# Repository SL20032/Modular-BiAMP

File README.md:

# Modular-BiAMP
Sample Modular Bi-AMP designed to work with Technics HD501 speakers (bc ampilifre in mine died). Project in active development.

## Modules
- Crosover PCB - Simple Active opamp based crosover providing 80db/dec attenuation. Components selected for 20 Hz to 3kHz passband for low freq part and 3kHz to 20kHz passband for high freq part.
- Power Amp PCB - Amplifire (AB-class) board using LM3886 for low frequence part (woofers) and LM4766 for high Frequency parts (tweeters)

## Fotos

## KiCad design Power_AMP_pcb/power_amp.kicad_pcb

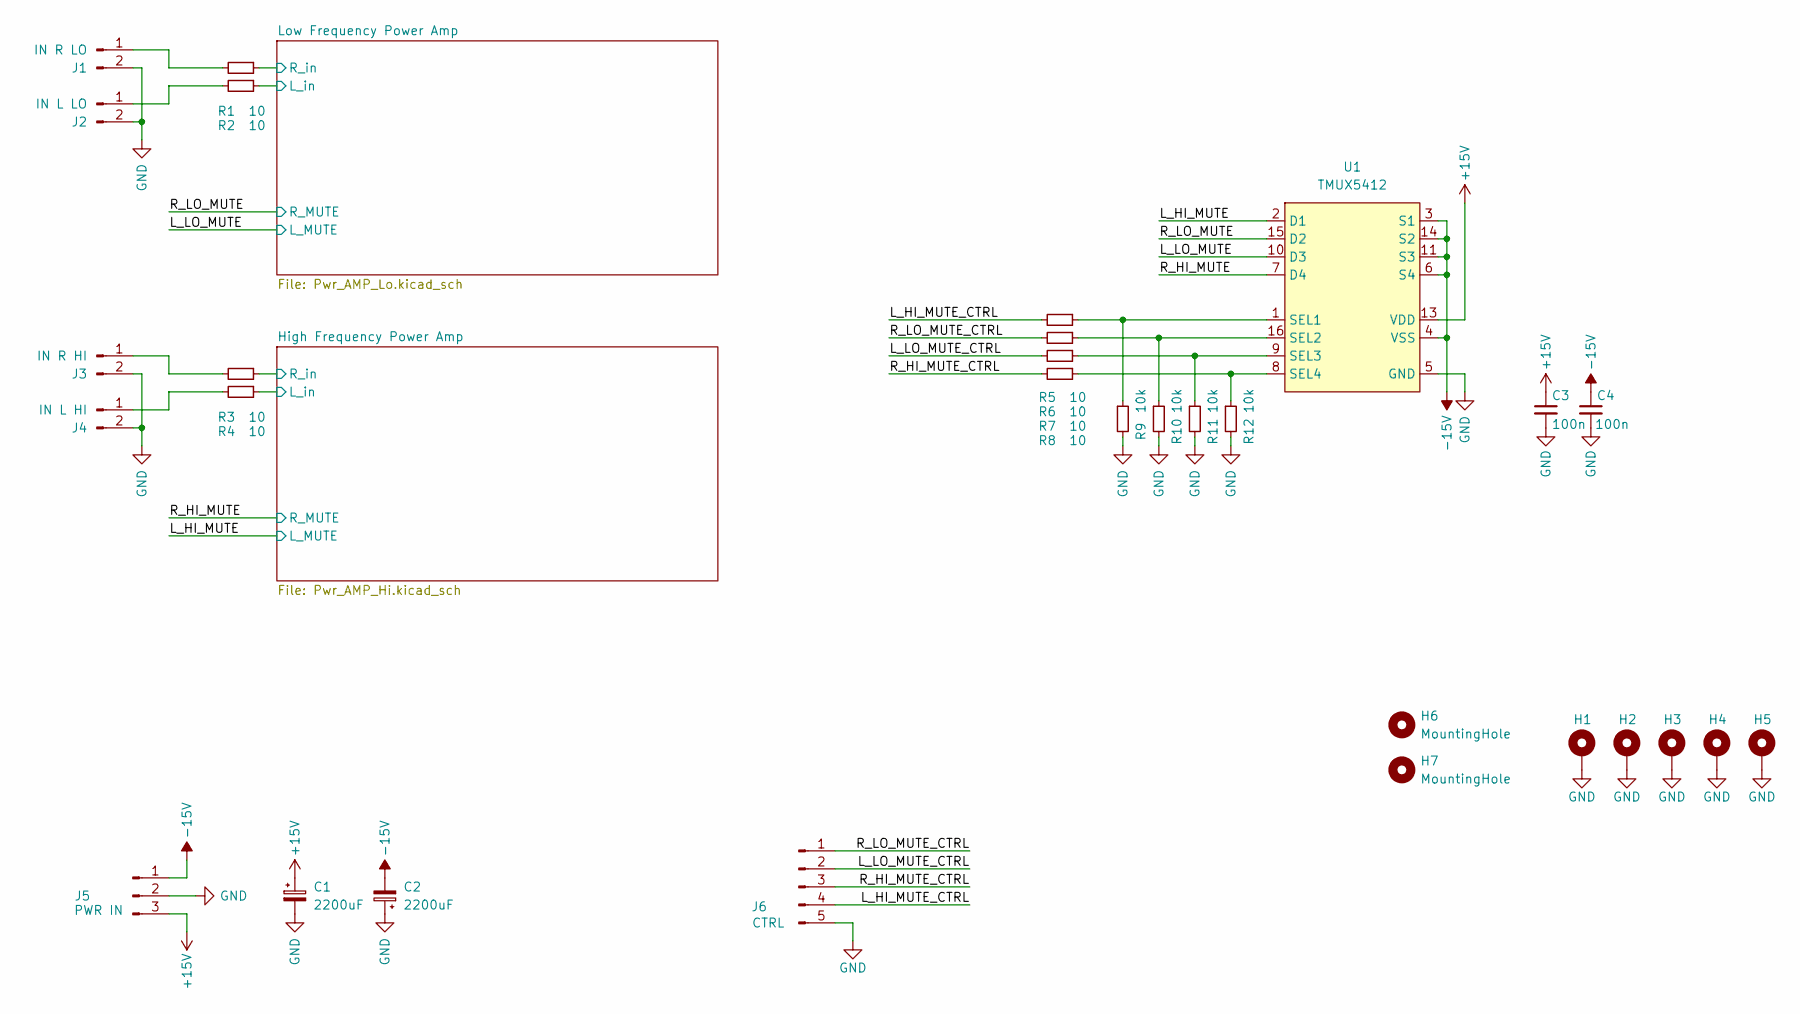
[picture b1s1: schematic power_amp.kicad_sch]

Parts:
C1, C2: 2200uF; CP_Radial_D12.5mm_P5.00mm
C3, C4: 100n; C_0805_2012Metric_Pad1.18x1.45mm_HandSolder
H1, H2, H3, H4, H5: MountingHole_Pad; MountingHole_3.2mm_M3_DIN965_Pad
H6, H7: MountingHole; Mounting_slots
J1: IN R LO; JST_NV_B02P-NV_1x02_P5.00mm_Vertical
J2: IN L LO; JST_NV_B02P-NV_1x02_P5.00mm_Vertical
J3: IN R HI; JST_NV_B02P-NV_1x02_P5.00mm_Vertical
J4: IN L HI; JST_NV_B02P-NV_1x02_P5.00mm_Vertical
J5: PWR IN; JST_NV_B03P-NV_1x03_P5.00mm_Vertical
J6: CTRL; PinHeader_1x05_P2.54mm_Vertical
R1, R2, R3, R4, R5, R6, R7, R8: 10; R_0805_2012Metric_Pad1.20x1.40mm_HandSolder
R9, R10, R11, R12: 10k; R_0805_2012Metric_Pad1.20x1.40mm_HandSolder
U1: TMUX5412; TSSOP-16_4.4x5mm_P0.65mm

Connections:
+15V: C1.1, C3.1, J5.3, U1.13 (VDD); also elsewhere on the board
-15V: C2.2, C4.1, J5.1, U1.3 (S1), U1.4 (VSS), U1.6 (S4), U1.11 (S3), U1.14 (S2); also elsewhere on the board
/High Frequency Power Amp/L_in: R4.1; also elsewhere on the board
/High Frequency Power Amp/R_in: R3.1; also elsewhere on the board
/L_HI_MUTE: U1.2 (D1); also elsewhere on the board
/L_HI_MUTE_CTRL: J6.4, R5.2
/L_LO_MUTE: U1.10 (D3); also elsewhere on the board
/L_LO_MUTE_CTRL: J6.2, R7.2
/Low Frequency Power Amp/L_in: R2.1; also elsewhere on the board
/Low Frequency Power Amp/R_in: R1.1; also elsewhere on the board
/R_HI_MUTE: U1.7 (D4); also elsewhere on the board
/R_HI_MUTE_CTRL: J6.3, R8.2
/R_LO_MUTE: U1.15 (D2); also elsewhere on the board
/R_LO_MUTE_CTRL: J6.1, R6.2
GND: C1.2, C2.1, C3.2, C4.2, H1.1, H2.1, H3.1, H4.1, H5.1, J1.2, J2.2, J3.2, J4.2, J5.2, J6.5, R9.2, R10.2, R11.2, R12.2, U1.5 (GND); also elsewhere on the board
unnamed: J1.1, R1.2
unnamed: J2.1, R2.2
unnamed: J3.1, R3.2
unnamed: J4.1, R4.2
unnamed: R5.1, R9.1, U1.1 (SEL1)
unnamed: R6.1, R10.1, U1.16 (SEL2)
unnamed: R7.1, R11.1, U1.9 (SEL3)
unnamed: R8.1, R12.1, U1.8 (SEL4)

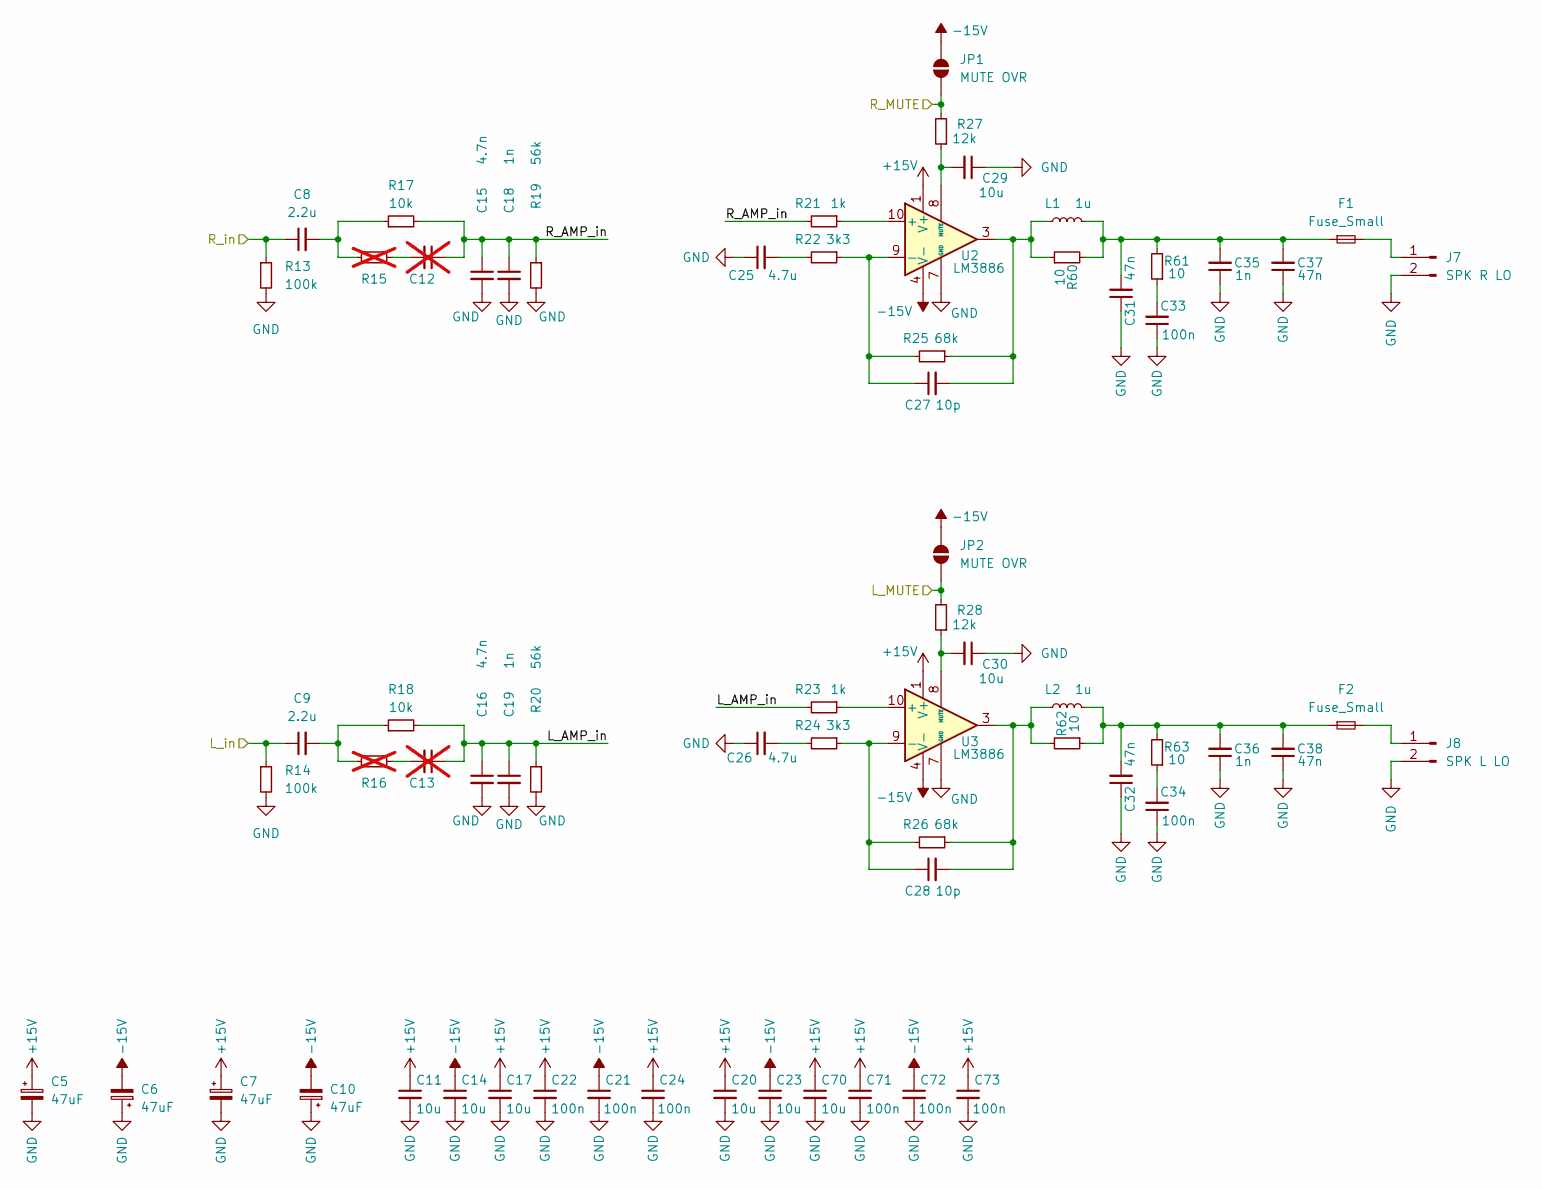
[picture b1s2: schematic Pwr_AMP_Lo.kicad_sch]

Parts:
C5, C6, C7, C10: 47uF; CP_Radial_D8.0mm_P3.50mm
C8, C9: 2.2u; C_Rect_L11.0mm_W5.1mm_P10.00mm_MKT
C11, C14, C17, C20, C23, C70: 10u; C_0805_2012Metric_Pad1.18x1.45mm_HandSolder
C12, C13: C_0805_2012Metric_Pad1.18x1.45mm_HandSolder; not fitted
C15, C16: 4.7n; C_Rect_L7.2mm_W2.5mm_P5.00mm_FKS2_FKP2_MKS2_MKP2
C18, C19, C35, C36: 1n; C_Rect_L7.2mm_W2.5mm_P5.00mm_FKS2_FKP2_MKS2_MKP2
C21, C22, C24, C71, C72, C73: 100n; C_0805_2012Metric_Pad1.18x1.45mm_HandSolder
C25, C26: 4.7u; C_Rect_L18.0mm_W7.0mm_P15.00mm_FKS3_FKP3
C27, C28: 10p; C_0805_2012Metric_Pad1.18x1.45mm_HandSolder
C29, C30: 10u; C_0805_2012Metric
C31, C32, C37, C38: 47n; C_Rect_L7.2mm_W2.5mm_P5.00mm_FKS2_FKP2_MKS2_MKP2
C33, C34: 100n; C_Rect_L7.2mm_W2.5mm_P5.00mm_FKS2_FKP2_MKS2_MKP2
F1, F2: Fuse_Small; Fuse_1206_3216Metric_Pad1.42x1.75mm_HandSolder
J7: SPK R LO; JST_NV_B02P-NV_1x02_P5.00mm_Vertical
J8: SPK L LO; JST_NV_B02P-NV_1x02_P5.00mm_Vertical
JP1, JP2: MUTE OVR; SolderJumper-2_P1.3mm_Open_RoundedPad1.0x1.5mm
L1, L2: 1u; L_Radial_D8.7mm_P5.00mm_Fastron_07HCP
R13, R14: 100k; R_0805_2012Metric_Pad1.20x1.40mm_HandSolder
R15, R16: R_0805_2012Metric_Pad1.20x1.40mm_HandSolder; not fitted
R17, R18: 10k; R_0805_2012Metric_Pad1.20x1.40mm_HandSolder
R19, R20: 56k; R_0805_2012Metric_Pad1.20x1.40mm_HandSolder
R21, R23: 1k; R_0805_2012Metric_Pad1.20x1.40mm_HandSolder
R22, R24: 3k3; R_0805_2012Metric_Pad1.20x1.40mm_HandSolder
R25, R26: 68k; R_0805_2012Metric_Pad1.20x1.40mm_HandSolder
R27, R28: 12k; R_0805_2012Metric_Pad1.20x1.40mm_HandSolder
R60, R61, R62, R63: 10; R_1206_3216Metric_Pad1.30x1.75mm_HandSolder
U2, U3: LM3886; TO-220F-11_P3.4x5.08mm_StaggerOdd_Lead5.08mm_Vertical

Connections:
+15V: C5.1, C7.1, C11.1, C17.1, C20.1, C22.1, C24.1, C70.1, C71.1, C73.1, U2.1 (V+), U2.5 (V+), U3.1 (V+), U3.5 (V+); also elsewhere on the board
-15V: C6.2, C10.2, C14.1, C21.1, C23.1, C72.1, JP1.2 (B), JP2.2 (B), U2.4 (V-), U3.4 (V-); also elsewhere on the board
/L_LO_MUTE: JP2.1 (A), R28.2; also elsewhere on the board
/Low Frequency Power Amp/L_AMP_in: C13.1, C16.1, C19.1, R18.2, R20.1, R23.2
/Low Frequency Power Amp/L_in: C9.1, R14.1; also elsewhere on the board
/Low Frequency Power Amp/R_AMP_in: C12.1, C15.1, C18.1, R17.2, R19.1, R21.2
/Low Frequency Power Amp/R_in: C8.1, R13.1; also elsewhere on the board
/R_LO_MUTE: JP1.1 (A), R27.2; also elsewhere on the board
GND: C5.2, C6.1, C7.2, C10.1, C11.2, C14.2, C15.2, C16.2, C17.2, C18.2, C19.2, C20.2, C21.2, C22.2, C23.2, C24.2, C25.1, C26.1, C29.1, C30.1, C31.1, C32.1, C33.1, C34.1, C35.1, C36.1, C37.1, C38.1, C70.2, C71.2, C72.2, C73.2, J7.2, J8.2, R13.2, R14.2, R19.2, R20.2, U2.7 (GND), U3.7 (GND); also elsewhere on the board
unnamed: C8.2, R15.2, R17.1
unnamed: C9.2, R16.2, R18.1
unnamed: C12.2, R15.1
unnamed: C13.2, R16.1
unnamed: C25.2, R22.2
unnamed: C26.2, R24.2
unnamed: C27.2, L1.1, R25.1, R60.1, U2.3
unnamed: C28.2, L2.1, R26.1, R62.2, U3.3
unnamed: C31.2, C35.2, C37.2, F1.1, L1.2, R60.2, R61.2
unnamed: C32.2, C36.2, C38.2, F2.1, L2.2, R62.1, R63.2
unnamed: C33.2, R61.1
unnamed: C34.2, R63.1
unnamed: F1.2, J7.1
unnamed: F2.2, J8.1
unnamed: R21.1, U2.10 (+)
unnamed: C27.1, R22.1, R25.2, U2.9 (-)
unnamed: C29.2, R27.1, U2.8 (MUTE)
unnamed: R23.1, U3.10 (+)
unnamed: C28.1, R24.1, R26.2, U3.9 (-)
unnamed: C30.2, R28.1, U3.8 (MUTE)

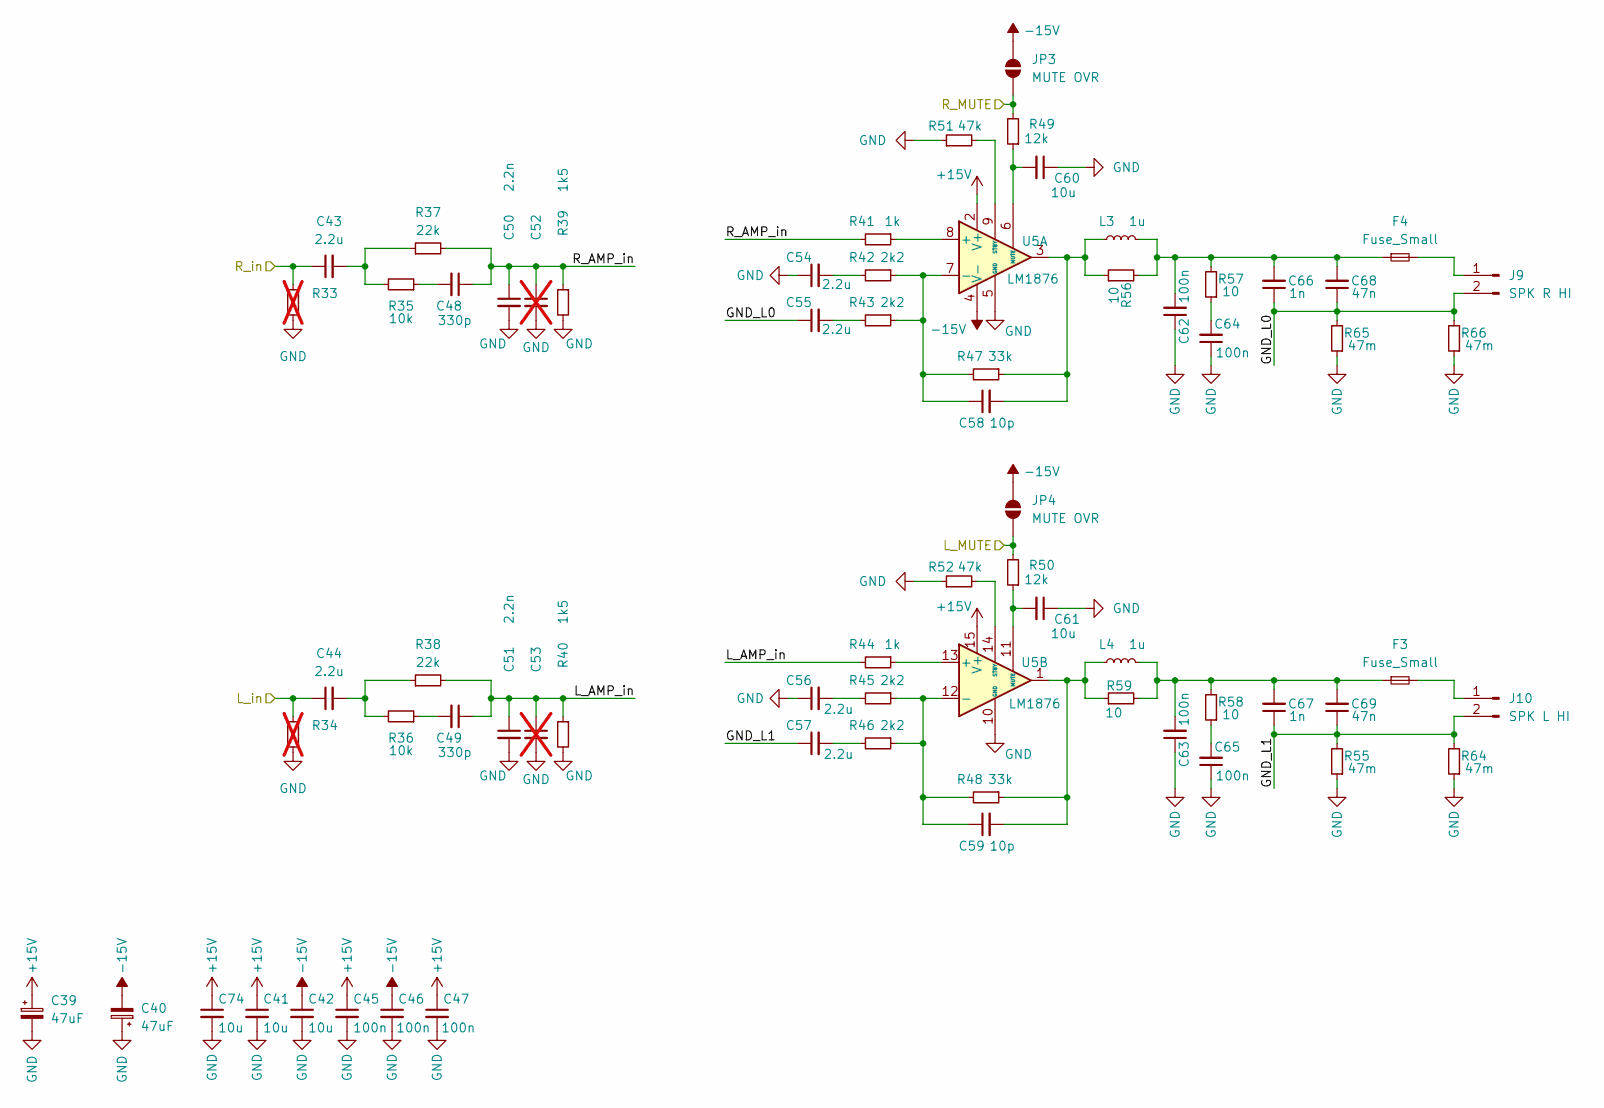
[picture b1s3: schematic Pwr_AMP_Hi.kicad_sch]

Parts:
C39, C40: 47uF; CP_Radial_D8.0mm_P3.50mm
C41, C42, C60, C61, C74: 10u; C_0805_2012Metric_Pad1.18x1.45mm_HandSolder
C43, C44, C54, C55, C56, C57: 2.2u; C_Rect_L11.0mm_W5.1mm_P10.00mm_MKT
C45, C46, C47: 100n; C_0805_2012Metric_Pad1.18x1.45mm_HandSolder
C48, C49: 330p; C_0805_2012Metric_Pad1.18x1.45mm_HandSolder
C50, C51: 2.2n; C_Rect_L7.2mm_W2.5mm_P5.00mm_FKS2_FKP2_MKS2_MKP2
C52, C53: C_Rect_L7.2mm_W2.5mm_P5.00mm_FKS2_FKP2_MKS2_MKP2; not fitted
C58, C59: 10p; C_0805_2012Metric_Pad1.18x1.45mm_HandSolder
C62, C63, C64, C65: 100n; C_Rect_L7.2mm_W2.5mm_P5.00mm_FKS2_FKP2_MKS2_MKP2
C66, C67: 1n; C_Rect_L7.2mm_W2.5mm_P5.00mm_FKS2_FKP2_MKS2_MKP2
C68, C69: 47n; C_Rect_L7.2mm_W2.5mm_P5.00mm_FKS2_FKP2_MKS2_MKP2
F3, F4: Fuse_Small; Fuse_1206_3216Metric_Pad1.42x1.75mm_HandSolder
J9: SPK R HI; JST_NV_B02P-NV_1x02_P5.00mm_Vertical
J10: SPK L HI; JST_NV_B02P-NV_1x02_P5.00mm_Vertical
JP3, JP4: MUTE OVR; SolderJumper-2_P1.3mm_Open_RoundedPad1.0x1.5mm
L3, L4: 1u; L_Radial_D8.7mm_P5.00mm_Fastron_07HCP
R33, R34: R_0805_2012Metric_Pad1.20x1.40mm_HandSolder; not fitted
R35, R36: 10k; R_0805_2012Metric_Pad1.20x1.40mm_HandSolder
R37, R38: 22k; R_0805_2012Metric_Pad1.20x1.40mm_HandSolder
R39, R40: 1k5; R_0805_2012Metric_Pad1.20x1.40mm_HandSolder
R41, R44: 1k; R_0805_2012Metric_Pad1.20x1.40mm_HandSolder
R42, R43, R45, R46: 2k2; R_0805_2012Metric_Pad1.20x1.40mm_HandSolder
R47, R48: 33k; R_0805_2012Metric_Pad1.20x1.40mm_HandSolder
R49, R50: 12k; R_0805_2012Metric_Pad1.20x1.40mm_HandSolder
R51, R52: 47k; R_0805_2012Metric_Pad1.20x1.40mm_HandSolder
R55, R64, R65, R66: 47m; R_1020_2550Metric_Pad1.33x5.20mm_HandSolder
R56, R57, R58, R59: 10; R_1206_3216Metric_Pad1.30x1.75mm_HandSolder
U5: LM1876; TO-220F-15_P2.54x5.08mm_StaggerOdd_Lead5.08mm_Vertical

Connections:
+15V: C39.1, C41.1, C45.1, C47.1, C74.1, U5.2 (V+), U5.15 (V+); also elsewhere on the board
-15V: C40.2, C42.1, C46.1, JP3.2 (B), JP4.2 (B), U5.4 (V-); also elsewhere on the board
/High Frequency Power Amp/GND_L0: C55.1, C66.1, C68.1, J9.2, R65.2, R66.2
/High Frequency Power Amp/GND_L1: C57.1, C67.1, C69.1, J10.2, R55.2, R64.2
/High Frequency Power Amp/L_AMP_in: C49.1, C51.1, C53.1, R38.2, R40.1, R44.2
/High Frequency Power Amp/L_in: C44.1, R34.1; also elsewhere on the board
/High Frequency Power Amp/R_AMP_in: C48.1, C50.1, C52.1, R37.2, R39.1, R41.2
/High Frequency Power Amp/R_in: C43.1, R33.1; also elsewhere on the board
/L_HI_MUTE: JP4.1 (A), R50.2; also elsewhere on the board
/R_HI_MUTE: JP3.1 (A), R49.2; also elsewhere on the board
GND: C39.2, C40.1, C41.2, C42.2, C45.2, C46.2, C47.2, C50.2, C51.2, C52.2, C53.2, C54.1, C56.1, C60.1, C61.1, C62.1, C63.1, C64.1, C65.1, C74.2, R33.2, R34.2, R39.2, R40.2, R51.1, R52.1, R55.1, R64.1, R65.1, R66.1, U5.5 (GND), U5.10 (GND); also elsewhere on the board
unnamed: C43.2, R35.2, R37.1
unnamed: C44.2, R36.2, R38.1
unnamed: C48.2, R35.1
unnamed: C49.2, R36.1
unnamed: C54.2, R42.2
unnamed: C55.2, R43.2
unnamed: C56.2, R45.2
unnamed: C57.2, R46.2
unnamed: C58.2, L3.1, R47.1, R56.1, U5.3
unnamed: C59.2, L4.1, R48.1, R59.1, U5.1
unnamed: C62.2, C66.2, C68.2, F4.1, L3.2, R56.2, R57.2
unnamed: C63.2, C67.2, C69.2, F3.1, L4.2, R58.2, R59.2
unnamed: C64.2, R57.1
unnamed: C65.2, R58.1
unnamed: F4.2, J9.1
unnamed: F3.2, J10.1
unnamed: R41.1, U5.8 (+)
unnamed: C58.1, R42.1, R43.1, R47.2, U5.7 (-)
unnamed: C60.2, R49.1, U5.6 (MUTE)
unnamed: R51.2, U5.9 (STBY)
unnamed: R44.1, U5.13 (+)
unnamed: C59.1, R45.1, R46.1, R48.2, U5.12 (-)
unnamed: C61.2, R50.1, U5.11 (MUTE)
unnamed: R52.2, U5.14 (STBY)

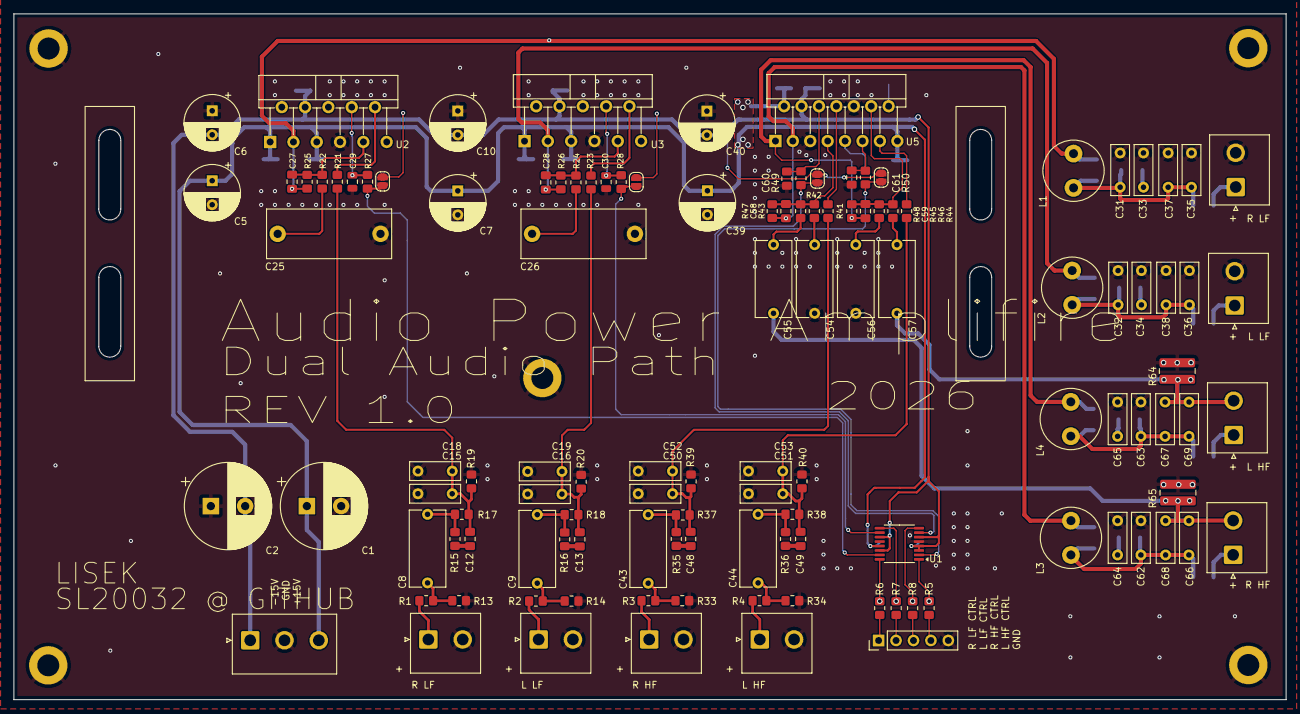
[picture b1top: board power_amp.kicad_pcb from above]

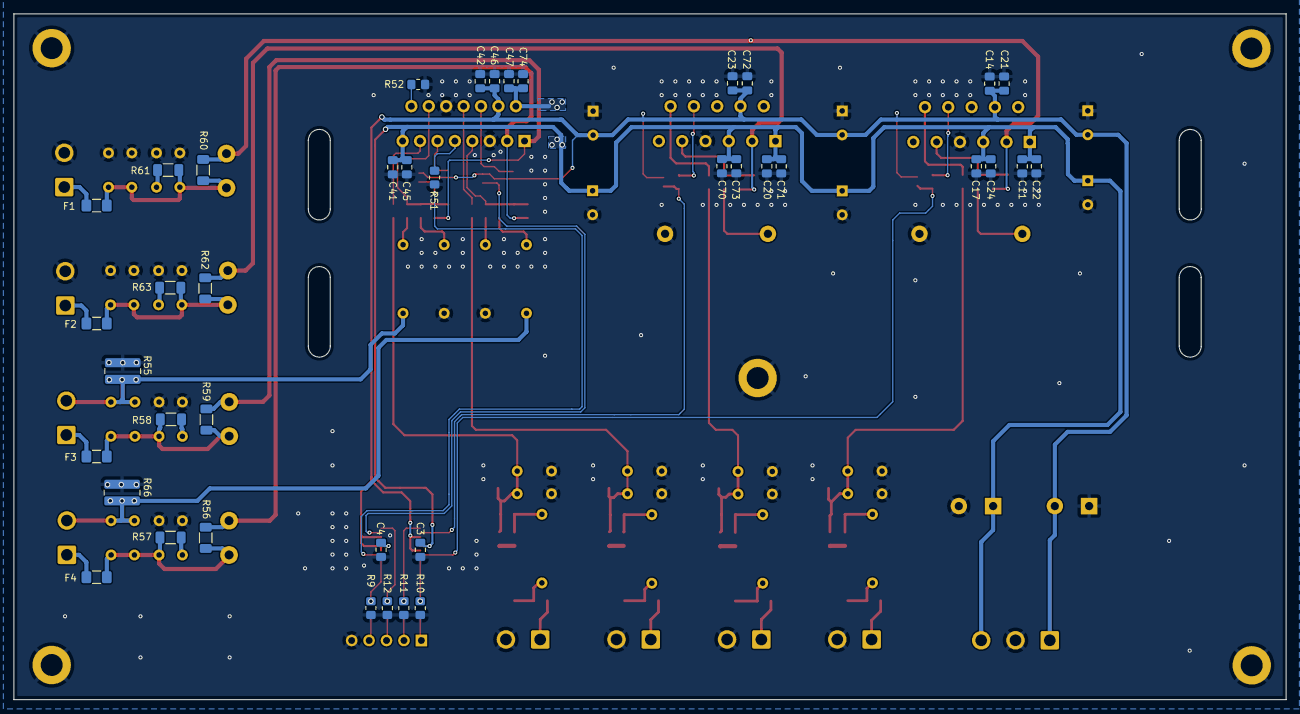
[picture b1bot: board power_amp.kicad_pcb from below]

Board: 2 copper layers, 185.5 x 100.0 mm, 167 parts (40 on the bottom side), 73 nets.

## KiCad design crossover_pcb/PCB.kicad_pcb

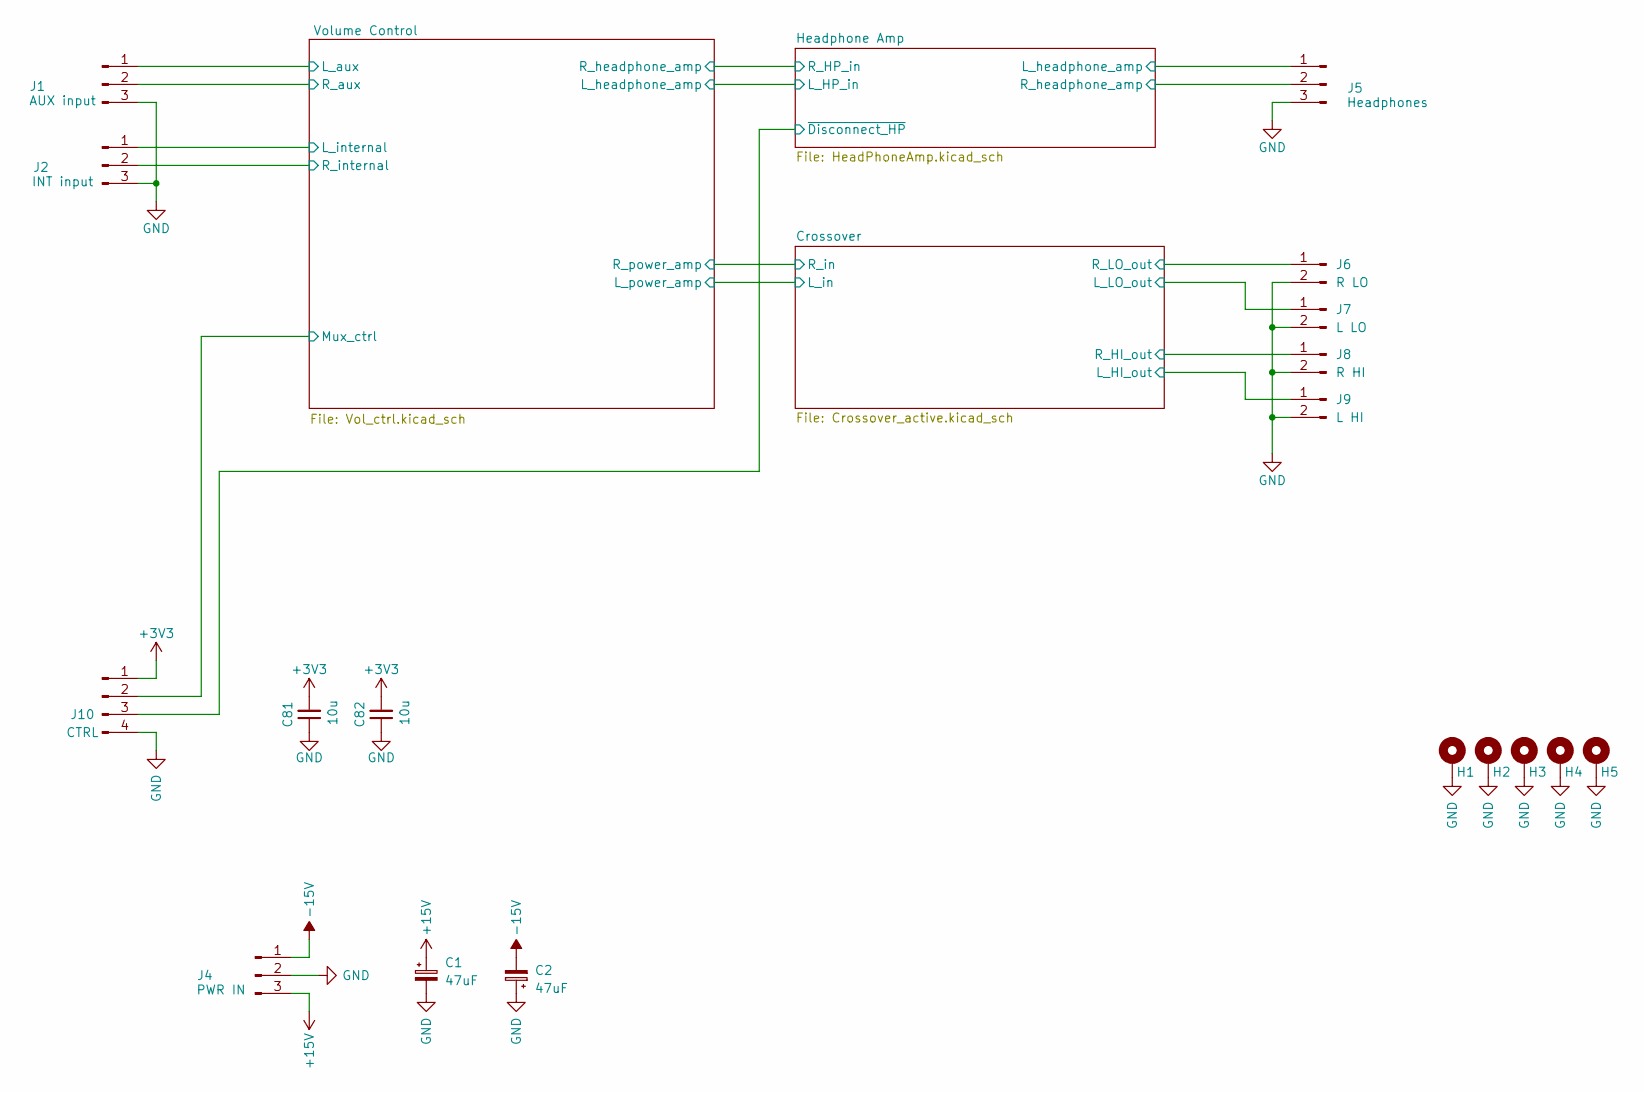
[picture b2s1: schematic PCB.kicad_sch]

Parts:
C1, C2: 47uF; CP_Radial_D8.0mm_P3.50mm
C81, C82: 10u; C_0805_2012Metric_Pad1.18x1.45mm_HandSolder
H1, H2, H3, H4, H5: MountingHole_Pad; MountingHole_3.2mm_M3_DIN965_Pad
J1: AUX input; PinSocket_1x03_P2.54mm_Vertical
J2: INT input; PinSocket_1x03_P2.54mm_Vertical
J4: PWR IN; JST_NV_B03P-NV_1x03_P5.00mm_Vertical
J5: Headphones; PinSocket_1x03_P2.54mm_Vertical
J6: R LO; JST_NV_B02P-NV_1x02_P5.00mm_Vertical
J7: L LO; JST_NV_B02P-NV_1x02_P5.00mm_Vertical
J8: R HI; JST_NV_B02P-NV_1x02_P5.00mm_Vertical
J9: L HI; JST_NV_B02P-NV_1x02_P5.00mm_Vertical
J10: CTRL; PinHeader_1x04_P2.54mm_Vertical

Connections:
+3V3: C81.2, C82.2, J10.1; also elsewhere on the board
+15V: C1.1, J4.3; also elsewhere on the board
-15V: C2.2, J4.1; also elsewhere on the board
/Crossover/L_HI_out: J9.1; also elsewhere on the board
/Crossover/L_LO_out: J7.1; also elsewhere on the board
/Crossover/R_HI_out: J8.1; also elsewhere on the board
/Crossover/R_LO_out: J6.1; also elsewhere on the board
/Headphone Amp/L_headphone_amp: J5.1; also elsewhere on the board
/Headphone Amp/R_headphone_amp: J5.2; also elsewhere on the board
/Headphone Amp/~Disconnect_HP: J10.3; also elsewhere on the board
/Volume Control/L_aux: J1.1; also elsewhere on the board
/Volume Control/L_internal: J2.1; also elsewhere on the board
/Volume Control/Mux_ctrl: J10.2; also elsewhere on the board
/Volume Control/R_aux: J1.2; also elsewhere on the board
/Volume Control/R_internal: J2.2; also elsewhere on the board
GND: C1.2, C2.1, C81.1, C82.1, H1.1, H2.1, H3.1, H4.1, H5.1, J1.3, J2.3, J4.2, J5.3, J6.2, J7.2, J8.2, J9.2, J10.4; also elsewhere on the board

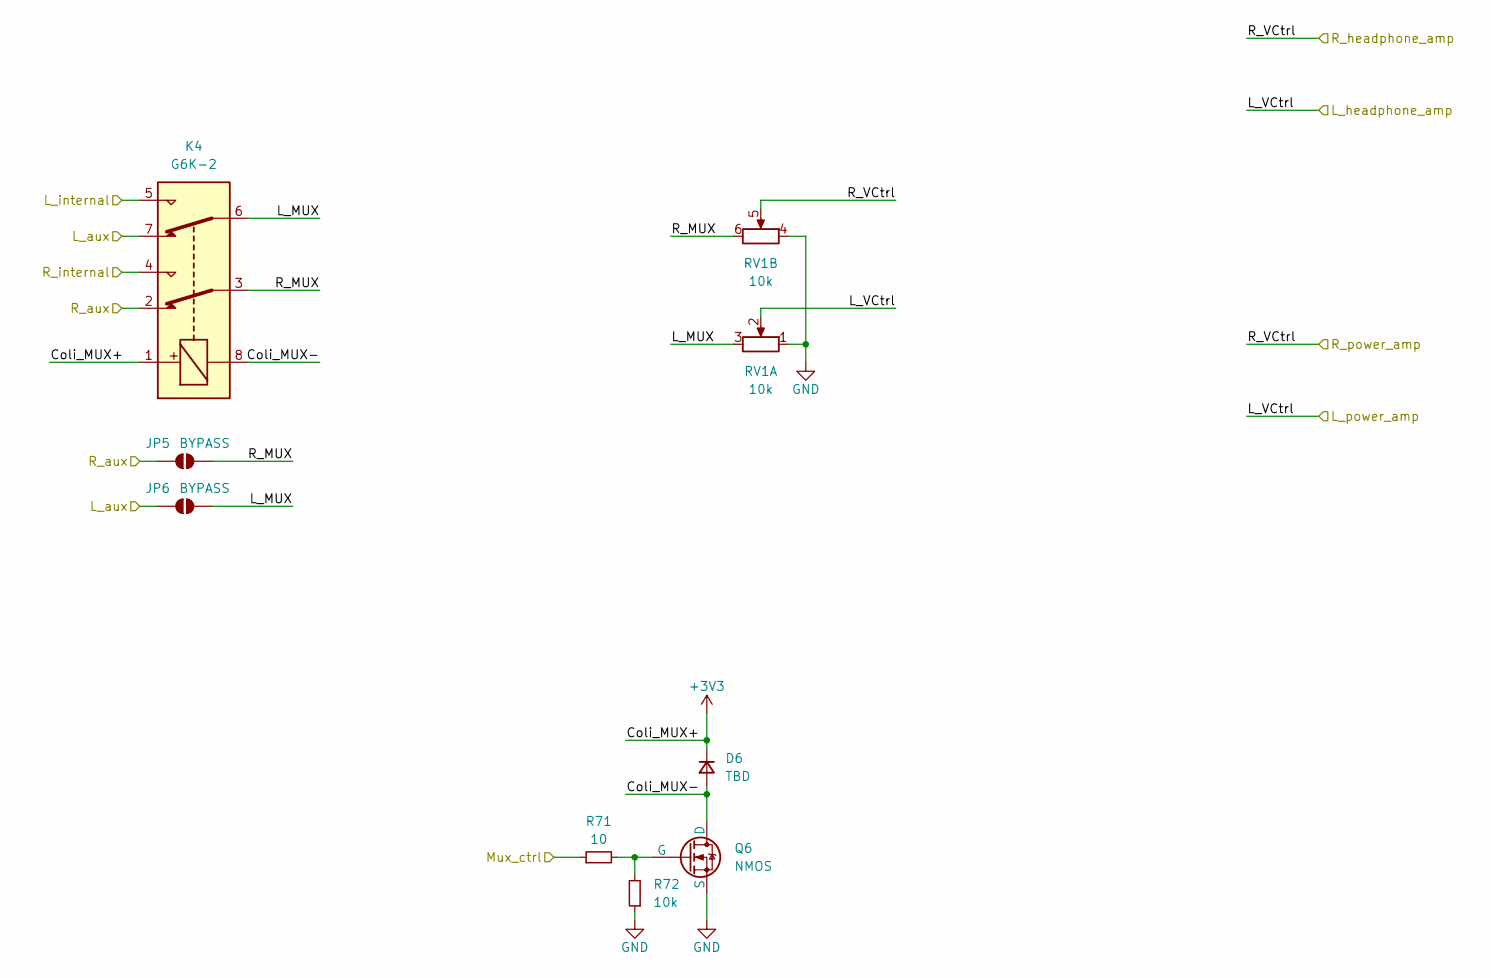
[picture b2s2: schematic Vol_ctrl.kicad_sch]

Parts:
D6: TBD; D_SOD-123
JP5, JP6: BYPASS; SolderJumper-2_P1.3mm_Open_RoundedPad1.0x1.5mm
K4: G6K-2; Relay_DPDT_Omron_G6K-2P
Q6: NMOS; SOT-23-Transistor
R71: 10; R_0805_2012Metric_Pad1.20x1.40mm_HandSolder
R72: 10k; R_0805_2012Metric_Pad1.20x1.40mm_HandSolder
RV1: 10k; Potentiometer_Piher_PC-16_Dual_Horizontal

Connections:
+3V3: D6.1 (K), K4.1; also elsewhere on the board
/Volume Control/Coli_MUX-: D6.2 (A), K4.8, Q6.1 (D)
/Volume Control/L_MUX: JP6.1 (A), K4.6, RV1.3
/Volume Control/L_VCtrl: RV1.2; also elsewhere on the board
/Volume Control/L_aux: JP6.2 (B), K4.7; also elsewhere on the board
/Volume Control/L_internal: K4.5; also elsewhere on the board
/Volume Control/Mux_ctrl: R71.1; also elsewhere on the board
/Volume Control/R_MUX: JP5.1 (A), K4.3, RV1.6
/Volume Control/R_VCtrl: RV1.5; also elsewhere on the board
/Volume Control/R_aux: JP5.2 (B), K4.2; also elsewhere on the board
/Volume Control/R_internal: K4.4; also elsewhere on the board
GND: Q6.3 (S), R72.1, RV1.1, RV1.4; also elsewhere on the board
unnamed: Q6.2 (G), R71.2, R72.2

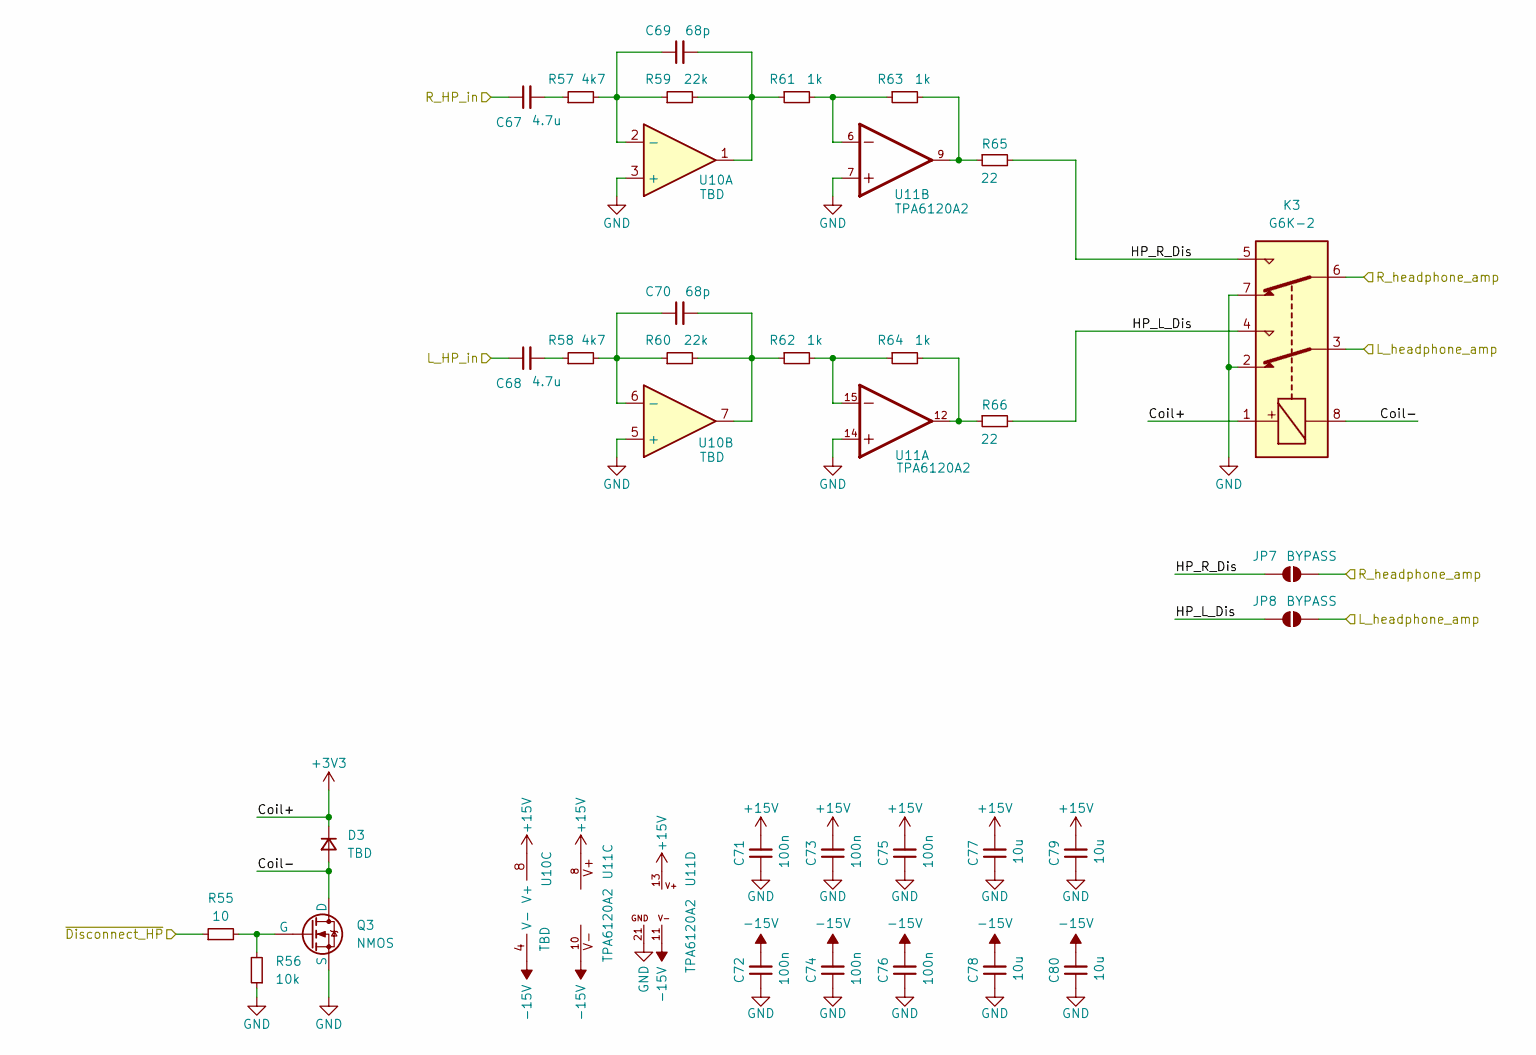
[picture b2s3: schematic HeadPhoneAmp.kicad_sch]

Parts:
C67, C68: 4.7u; C_Rect_L18.0mm_W7.0mm_P15.00mm_FKS3_FKP3
C69, C70: 68p; C_0805_2012Metric_Pad1.18x1.45mm_HandSolder
C71, C72, C73, C74, C75, C76: 100n; C_0805_2012Metric_Pad1.18x1.45mm_HandSolder
C77, C78, C79, C80: 10u; C_0805_2012Metric_Pad1.18x1.45mm_HandSolder
D3: TBD; D_SOD-123
JP7, JP8: BYPASS; SolderJumper-2_P1.3mm_Open_RoundedPad1.0x1.5mm
K3: G6K-2; Relay_DPDT_Omron_G6K-2P
Q3: NMOS; SOT-23-Transistor
R55: 10; R_0805_2012Metric_Pad1.20x1.40mm_HandSolder
R56: 10k; R_0805_2012Metric_Pad1.20x1.40mm_HandSolder
R57, R58: 4k7; R_0805_2012Metric_Pad1.20x1.40mm_HandSolder
R59, R60: 22k; R_0805_2012Metric_Pad1.20x1.40mm_HandSolder
R61, R62, R63, R64: 1k; R_0805_2012Metric_Pad1.20x1.40mm_HandSolder
R65, R66: 22; R_0805_2012Metric_Pad1.20x1.40mm_HandSolder
U10: TBD; SO-8_3.9x4.9mm_P1.27mm
U11: TPA6120A2; SOIC-20-EP

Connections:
+3V3: D3.1 (K), K3.1; also elsewhere on the board
+15V: C71.2, C73.2, C75.2, C77.2, C79.2, U10.8 (V+), U11.8, U11.13; also elsewhere on the board
-15V: C72.2, C74.2, C76.2, C78.2, C80.2, U10.4 (V-), U11.10, U11.11; also elsewhere on the board
/Headphone Amp/Coil-: D3.2 (A), K3.8, Q3.1 (D)
/Headphone Amp/HP_L_Dis: JP8.2 (B), K3.4, R66.2
/Headphone Amp/HP_R_Dis: JP7.2 (B), K3.5, R65.2
/Headphone Amp/L_headphone_amp: JP8.1 (A), K3.3; also elsewhere on the board
/Headphone Amp/R_headphone_amp: JP7.1 (A), K3.6; also elsewhere on the board
/Headphone Amp/~Disconnect_HP: R55.1; also elsewhere on the board
/Volume Control/L_VCtrl: C68.1; also elsewhere on the board
/Volume Control/R_VCtrl: C67.1; also elsewhere on the board
GND: C71.1, C72.1, C73.1, C74.1, C75.1, C76.1, C77.1, C78.1, C79.1, C80.1, K3.2, K3.7, Q3.3 (S), R56.1, U10.3 (+), U10.5 (+), U11.7, U11.14, U11.21, U11.P$1, U11.P$2, U11.P$3, U11.P$4; also elsewhere on the board
unnamed: C67.2, R57.1
unnamed: C68.2, R58.1
unnamed: C69.2, R59.2, R61.1, U10.1
unnamed: C70.2, R60.2, R62.1, U10.7
unnamed: Q3.2 (G), R55.2, R56.2
unnamed: R61.2, R63.1, U11.6
unnamed: R62.2, R64.1, U11.15
unnamed: R63.2, R65.1, U11.9
unnamed: R64.2, R66.1, U11.12
unnamed: C69.1, R57.2, R59.1, U10.2 (-)
unnamed: C70.1, R58.2, R60.1, U10.6 (-)
